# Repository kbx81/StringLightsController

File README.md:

# kbx's String Lights Controller with ESP32 <!-- omit in toc -->

This repository contains [KiCad](https://kicad.org) project files for a PCB which can control RGB/W (patio) [string lights I bought from Amazon](https://a.co/d/7NtrBNi).

The LEDs used in these strings are unique in that there is **no dedicated data wire** via which data is sent to the addressable RGB LEDs the string consists of.

I've posted a short [video](https://youtu.be/82iJrEUkA1w) demo of the controller/lights in action on [YouTube](https://youtube.com).

## Table of Contents  <!-- omit in toc -->
- [Overview](#overview)
- [The Signal](#the-signal)
- [The ESPHome Configuration](#the-esphome-configuration)
- [The Box](#the-box)
- [The Question](#the-question)
- [Legal stuff and License](#legal-stuff-and-license)

## Overview

These string lights consist of LED bulbs which contain both an addressable RGB LED as well as ordinary white LEDs. A 433 MHz wireless handheld remote is provided for control of color, intensity, etc. One day, one of my strings went completely dead; I already had a desire to make these work directly within [Home Assistant](https://www.home-assistant.io) and so now this project exists.

The LEDs used in these strings are unique in that there is _no dedicated data wire_ via which data is sent to the addressable RGB LEDs the string consists of; each bulb has only/exactly two electrical contacts and all of the bulbs are electrically connected in parallel.

They can operate in one of two modes: RGB or white-only.

In RGB mode, data is sent by way of toggling the 5-volt supply between 5 volts and 2.5 volts; specific timing is used to differentiate between a logical `0` and `1`, similar to WS281x LEDs.

In white mode, the polarity of the power supply to the bulbs in the string is reversed, deactivating the RGB LED and instead lighting up the white LEDs. In this mode, simple PWM is then used to dim the white LEDs.

Given that the polarity of the power supply to the bulbs is used to determine the mode (RGB vs. white), it is not possible to use both the white and RGB modes simultaneously.

## The Signal

Because there is no dedicated data wire and because all of the LEDs are electrically connected in parallel, these LEDs are "pre-addressed", meaning each one is (somehow) assigned a number that is (permanently?) embedded in the LED. (It may be possible to change this address but I can't seem to find any specific documentation for these LEDs.)

The structure of the data sent to these particular LEDs is quite simple. It consists of:

- A 3-bit header identifying which LED address the RGB data that follows is for
- 24 bits containing the RGB values for the LED address indicated by the header (above):
  - Eight bits for green
  - Eight bits for red
  - Eight bits for blue

These specific strings (as linked above) are shipped with LEDs that have one of four addresses (0, 1, 2 or 3); with four addresses on the line, a complete transmission (to update all RGB LEDs in the string) consists of four 27-bit packets (as described above).

## The ESPHome Configuration

Given the complexity of operating these LED bulbs, I needed a custom ESPHome component to control/drive the electronics necessary to operate them -- attempting to operate them manually by way of switches is actually dangerous as [the H-bridge configuration](StringLightsController.pdf) can produce in a direct short across the power supply. They're not useful if the magic smoke comes out.

I've created a repository for my [ESPHome custom/external components](https://github.com/kbx81/esphome_custom_components). Specifically, the [`dop_led_plus_h_bridge`](https://github.com/kbx81/esphome_custom_components/tree/main/components/dop_led_plus_h_bridge) external component exists for just this purpose/project. If you take the time to build one (or more) of these PCBs, I highly recommend using it!

As for ESPHome configuration for these, I've created a separate repository for my [ESPHome](https://esphome.io) [configurations](https://github.com/kbx81/esphome-configs); the specific configuration I'm using with this board is [here](https://github.com/kbx81/esphome-configs/blob/c437e0f0ec9d37ab05d2a22e129756eb35faa67d/shared/esp-lights-string-base.yaml) and I'll also point you more directly to the `dop_led_plus_h_bridge` configuration within that file [here](https://github.com/kbx81/esphome-configs/blob/c437e0f0ec9d37ab05d2a22e129756eb35faa67d/shared/esp-lights-string-base.yaml#L468-L481).

## The Box

Any real project needs an enclosure. I drew up a simple [mounting plate](StringLightsPSUMountingPlate.3mf) to securely hold the PCB and power supply inside of a BUD Industries `PIP-11767` IP-67 enclosure which I also got from [Amazon](https://www.amazon.com/gp/product/B00OG1X29U/). Add some [cable glands](https://www.amazon.com/gp/product/B06Y5HXP2H/) to route the cables in/out of the enclosure and you've got a wonderful little control box that uses [ESPHome](https://esphome.io) and [Home Assistant](https://www.home-assistant.io) to operate these strings of lights!

## The Question

This is what's inside of one of these LED bulbs:

Where on Earth do these particular RGB LEDs come from??? I'm not aware of any sellers and a bit of searching around the 'net has revealed no sources. If you happen to know where to source these, please let me know! I'd be quite interested to pick some up to play with, especially if I could get LEDs with more than four addresses and/or get some real documentation on them.

## Legal stuff and License

Everything you see here is provided to you free of charge. You are free to use it however you please within the constraints of the license -- but you do so at your own risk.

The contents of this repository are licensed under the [Creative Commons Attribution-ShareAlike 4.0 International License](http://creativecommons.org/licenses/by-sa/4.0/).

_Thanks for visiting!_

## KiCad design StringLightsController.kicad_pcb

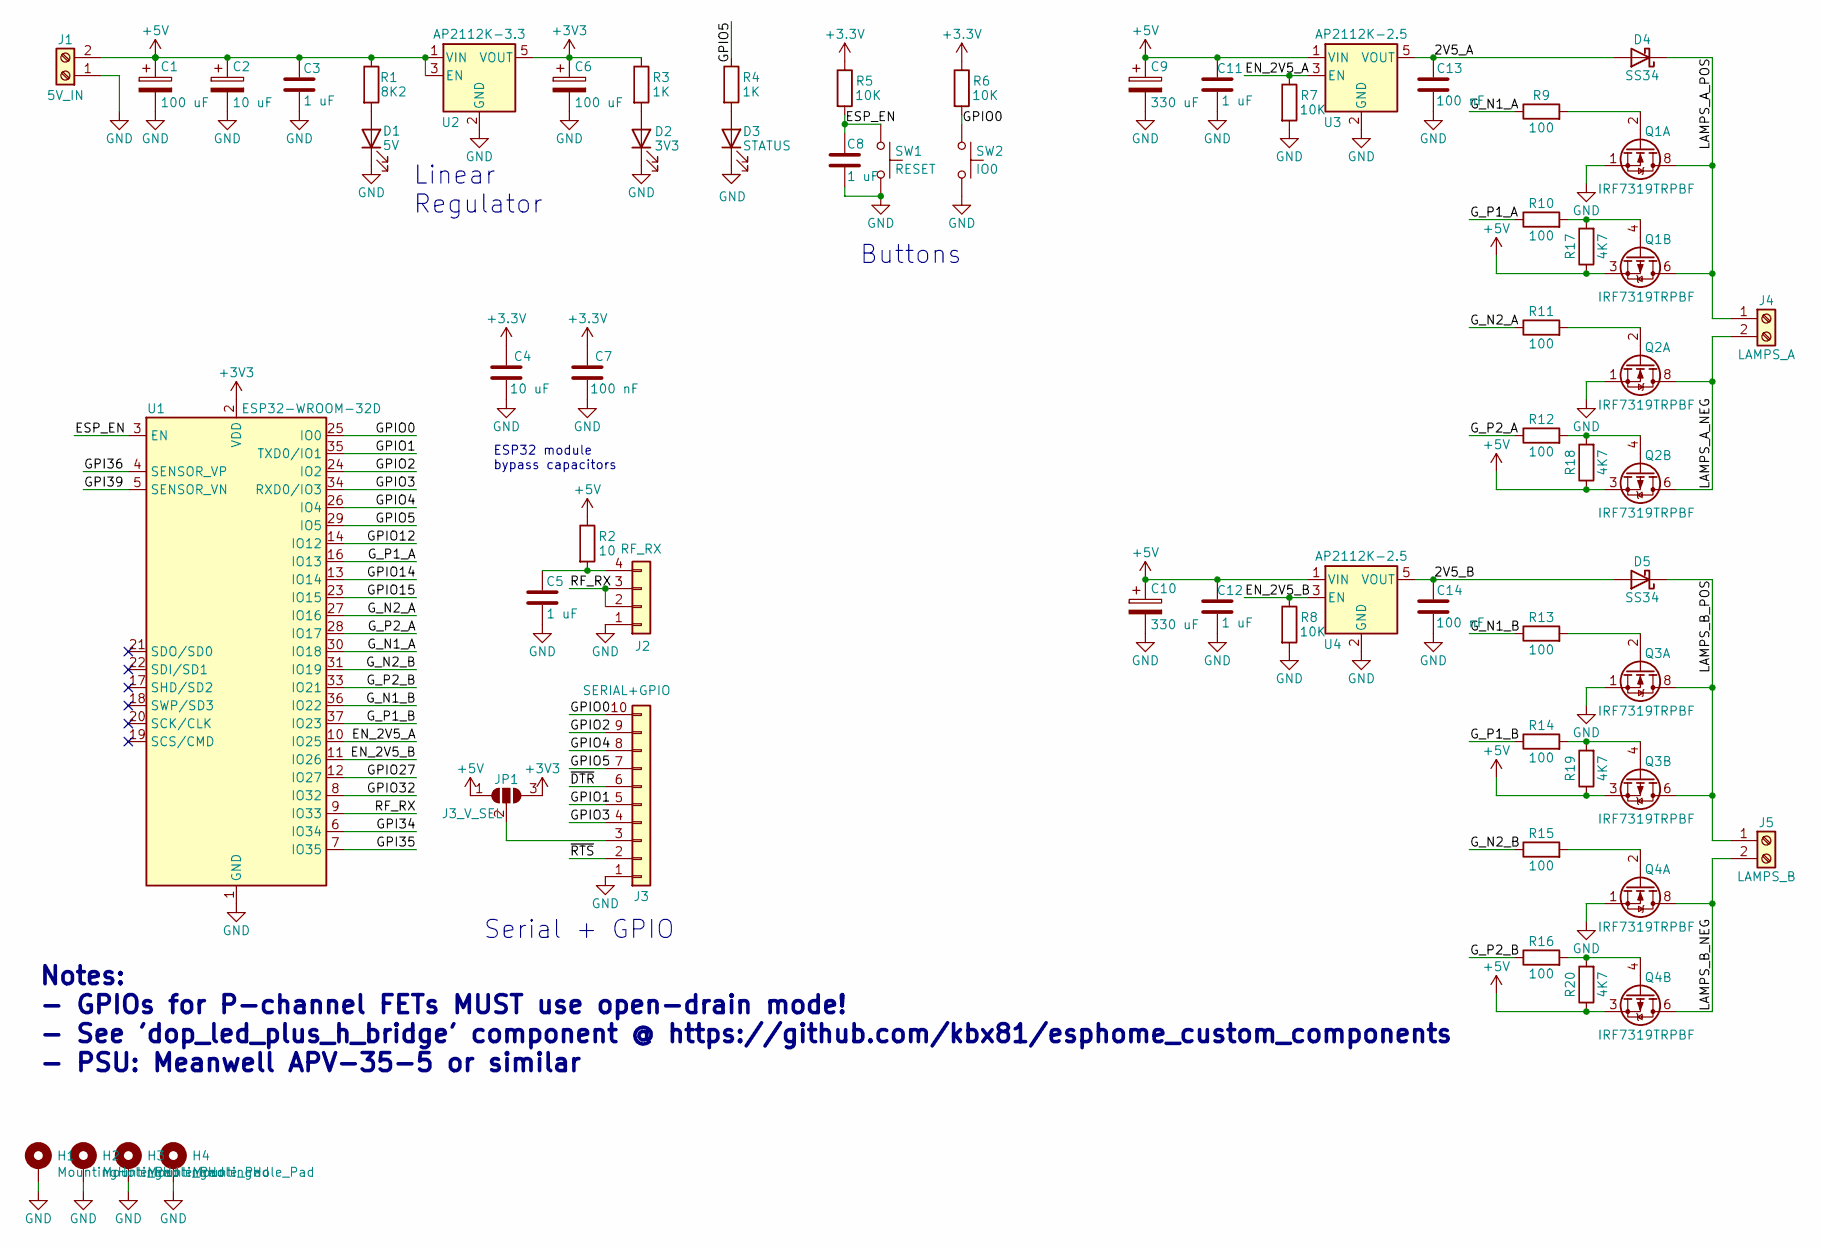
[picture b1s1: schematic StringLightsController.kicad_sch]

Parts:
C1, C6: 100 uF; CP_Elec_5x5.4; MPN1 UWR1A101MCL1GB
C2: 10 uF; CP_Elec_4x5.8; MPN1 AFK106M25B12T-F
C3, C5, C8, C11, C12: 1 uF; C_0805_2012Metric; MPN1 C2012X5R1E105M125AA
C4: 10 uF; C_0805_2012Metric; MPN1 GRM21BC81C106ME15L
C7, C13, C14: 100 nF; C_0805_2012Metric; MPN1 CC0805KRX7R7BB104
C9, C10: 330 uF; CP_Elec_6.3x7.7; MPN1 UWT1A102MNL1GS
D1: 5V; LED_0805_2012Metric; MPN1 597-6901-607F
D2: 3V3; LED_0805_2012Metric; MPN1 597-6901-607F
D3: STATUS; LED_0805_2012Metric; MPN1 APT2012EC
D4, D5: SS34; D_SOD-123; MPN1 SS34FA
H1, H2, H3, H4: MountingHole_Pad; MountingHole_3.2mm_M3_Pad_Via
J1: 5V_IN; TerminalBlock_Phoenix_PT-1,5-2-3.5-H_1x02_P3.50mm_Horizontal
J2: RF_RX; PinSocket_1x04_P2.54mm_Vertical
J3: SERIAL+GPIO; PinSocket_1x10_P2.54mm_Vertical
J4: LAMPS_A; TerminalBlock_Phoenix_PT-1,5-2-3.5-H_1x02_P3.50mm_Horizontal
J5: LAMPS_B; TerminalBlock_Phoenix_PT-1,5-2-3.5-H_1x02_P3.50mm_Horizontal
JP1: J3_V_SEL; SolderJumper-3_P1.3mm_Open_RoundedPad1.0x1.5mm
Q1, Q2, Q3, Q4: IRF7319TRPBF; SOIC-8_3.9x4.9mm_P1.27mm; MPN1 IRF7319TRPBF
R1: 8K2; R_0805_2012Metric; MPN1 RT0805FRE078K2L
R2: 10; R_0805_2012Metric; MPN1 RC0805FR-0710RL
R3, R4: 1K; R_0805_2012Metric; MPN1 RC0805FR-071KL
R5, R6, R7, R8: 10K; R_0805_2012Metric; MPN1 RC0805FR-0710KL
R9, R10, R11, R12, R13, R14, R15, R16: 100; R_0805_2012Metric; MPN1 RC0805FR-07100RL
R17, R18, R19, R20: 4K7; R_0805_2012Metric; MPN1 RC0805FR-074K7L
SW1: RESET; SW_Push_1P1T_NO_CK_KMR2; MPN1 KMR221GLFS
SW2: IO0; SW_Push_1P1T_NO_CK_KMR2; MPN1 KMR221GLFS
U1: ESP32-WROOM-32D; ESP32-WROOM-32; MPN1 ESP32-WROOM-32D-N4
U2: AP2112K-3.3; SOT-23-5; MPN1 AP2112K-3.3
U3, U4: AP2112K-2.5; SOT-23-5; MPN1 AP2112K-2.5

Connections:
+5V: C1.1, C2.1, C3.1, C9.1, C10.1, C11.1, C12.1, J1.2, JP1.1 (A), Q1.3 (1), Q2.3 (1), Q3.3 (1), Q4.3 (1), R1.1, R2.1, R17.1, R18.1, R19.1, R20.1, U2.1 (VIN), U2.3 (EN), U3.1 (VIN), U4.1 (VIN)
/2V5_A: C13.1, D4.2 (A), U3.5 (VOUT)
/2V5_B: C14.1, D5.2 (A), U4.5 (VOUT)
/EN_2V5_A: R7.1, U1.10 (IO25), U3.3 (EN)
/EN_2V5_B: R8.1, U1.11 (IO26), U4.3 (EN)
/ESP_EN: C8.1, R5.2, SW1.1, U1.3 (EN)
/GPI34: U1.6 (IO34)
/GPI35: U1.7 (IO35)
/GPI36: U1.4 (SENSOR_VP)
/GPI39: U1.5 (SENSOR_VN)
/GPIO0: J3.10, R6.2, SW2.1, U1.25 (IO0)
/GPIO1: J3.5, U1.35 (TXD0/IO1)
/GPIO2: J3.9, U1.24 (IO2)
/GPIO3: J3.4, U1.34 (RXD0/IO3)
/GPIO4: J3.8, U1.26 (IO4)
/GPIO5: J3.7, R4.1, U1.29 (IO5)
/GPIO12: U1.14 (IO12)
/GPIO14: U1.13 (IO14)
/GPIO15: U1.23 (IO15)
/GPIO27: U1.12 (IO27)
/GPIO32: U1.8 (IO32)
/G_N1_A: R9.1, U1.30 (IO18)
/G_N1_B: R13.1, U1.36 (IO22)
/G_N2_A: R11.1, U1.27 (IO16)
/G_N2_B: R15.1, U1.31 (IO19)
/G_P1_A: R10.1, U1.16 (IO13)
/G_P1_B: R14.1, U1.37 (IO23)
/G_P2_A: R12.1, U1.28 (IO17)
/G_P2_B: R16.1, U1.33 (IO21)
/LAMPS_A_NEG: J4.2, Q2.5 (D), Q2.6 (D), Q2.7 (D), Q2.8 (D)
/LAMPS_A_POS: D4.1 (K), J4.1, Q1.5 (D), Q1.6 (D), Q1.7 (D), Q1.8 (D)
/LAMPS_B_NEG: J5.2, Q4.5 (D), Q4.6 (D), Q4.7 (D), Q4.8 (D)
/LAMPS_B_POS: D5.1 (K), J5.1, Q3.5 (D), Q3.6 (D), Q3.7 (D), Q3.8 (D)
/RF_RX: J2.2, J2.3, U1.9 (IO33)
/~DTR: J3.6
/~RTS: J3.2
GND: C1.2, C2.2, C3.2, C4.2, C5.2, C6.2, C7.2, C8.2, C9.2, C10.2, C11.2, C12.2, C13.2, C14.2, D1.1 (K), D2.1 (K), D3.1 (K), H1.1, H2.1, H3.1, H4.1, J1.1, J2.1, J3.1, Q1.1 (S), Q2.1 (S), Q3.1 (S), Q4.1 (S), R7.2, R8.2, SW1.2, SW2.2, U1.1 (GND), U1.15 (GND), U1.38 (GND), U1.39 (GND), U2.2 (GND), U3.2 (GND), U4.2 (GND)
unnamed: C5.1, J2.4, R2.2
unnamed: D1.2 (A), R1.2
unnamed: D2.2 (A), R3.2
unnamed: D3.2 (A), R4.2
unnamed: J3.3, JP1.2 (C)
unnamed: Q1.2 (G), R9.2
unnamed: Q1.4 (G), R10.2, R17.2
unnamed: Q2.2 (G), R11.2
unnamed: Q2.4 (G), R12.2, R18.2
unnamed: Q3.2 (G), R13.2
unnamed: Q3.4 (G), R14.2, R19.2
unnamed: Q4.2 (G), R15.2
unnamed: Q4.4 (G), R16.2, R20.2

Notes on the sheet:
ESP32 module bypass capacitors
Serial + GPIO
Linear Regulator
Buttons
Notes: - GPIOs for P-channel FETs MUST use open-drain mode! - See 'dop_led_plus_h_bridge' component @ https://github.com/kbx81/esphome_custom_components - PSU: Meanwell APV-35-5 or similar

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
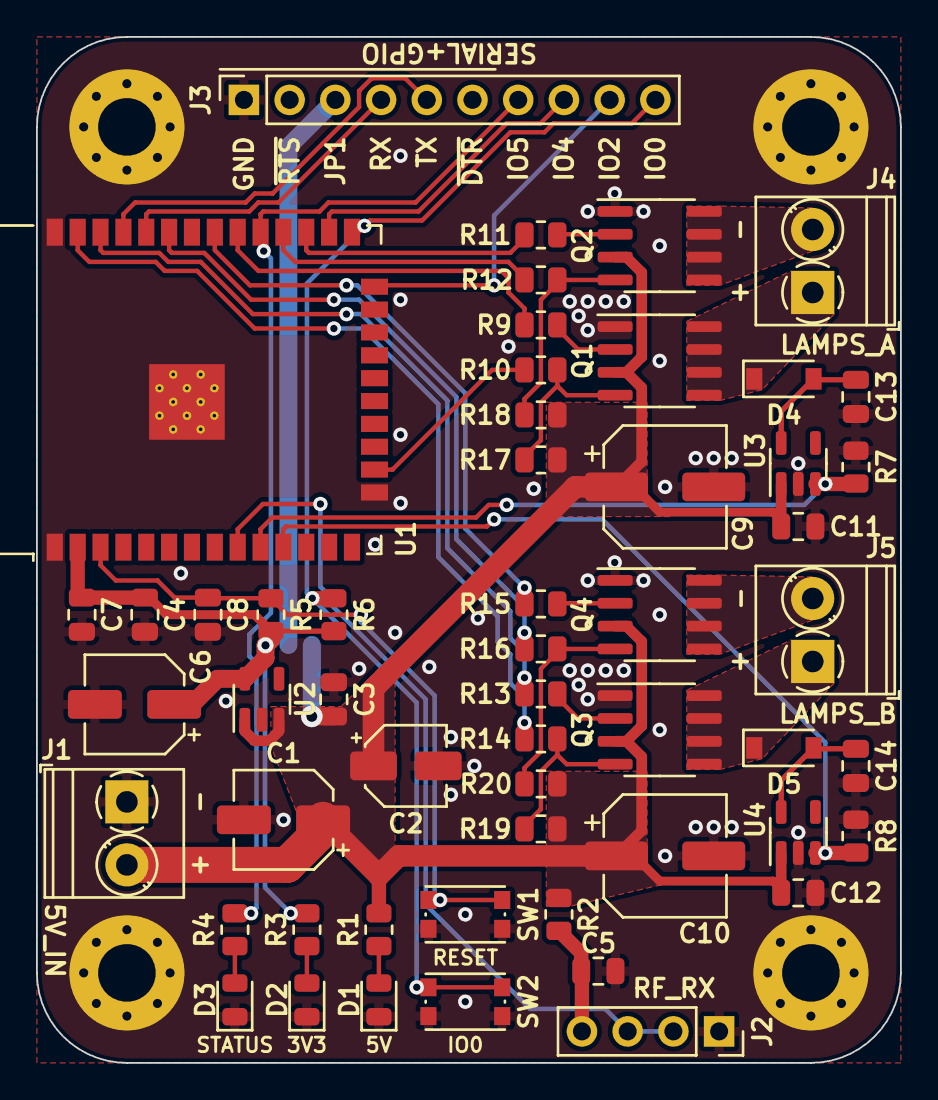
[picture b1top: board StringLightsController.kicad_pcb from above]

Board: 2 copper layers, 48.0 x 57.0 mm, 59 parts (1 on the bottom side), 40 nets.

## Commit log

2023-06-19 Fix links
2023-06-19 Add BoM
